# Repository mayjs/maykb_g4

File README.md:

# maykb G4

This is my fourth custom split keyboard, this time using an ANSI layout.

## Caveats / Known Issues

In its current form, the level shifter for the WS2812b LEDs does NOT work.
With most clones, you can just remove the Mosfet and the two resistors next to it and bridge the microcontroller LED data input directly to the LED data input.
Some LEDs might not properly recognize the 3.3V signal though, so you might see some glitches due to this.

Otherwise, the keyboard works without any issues.

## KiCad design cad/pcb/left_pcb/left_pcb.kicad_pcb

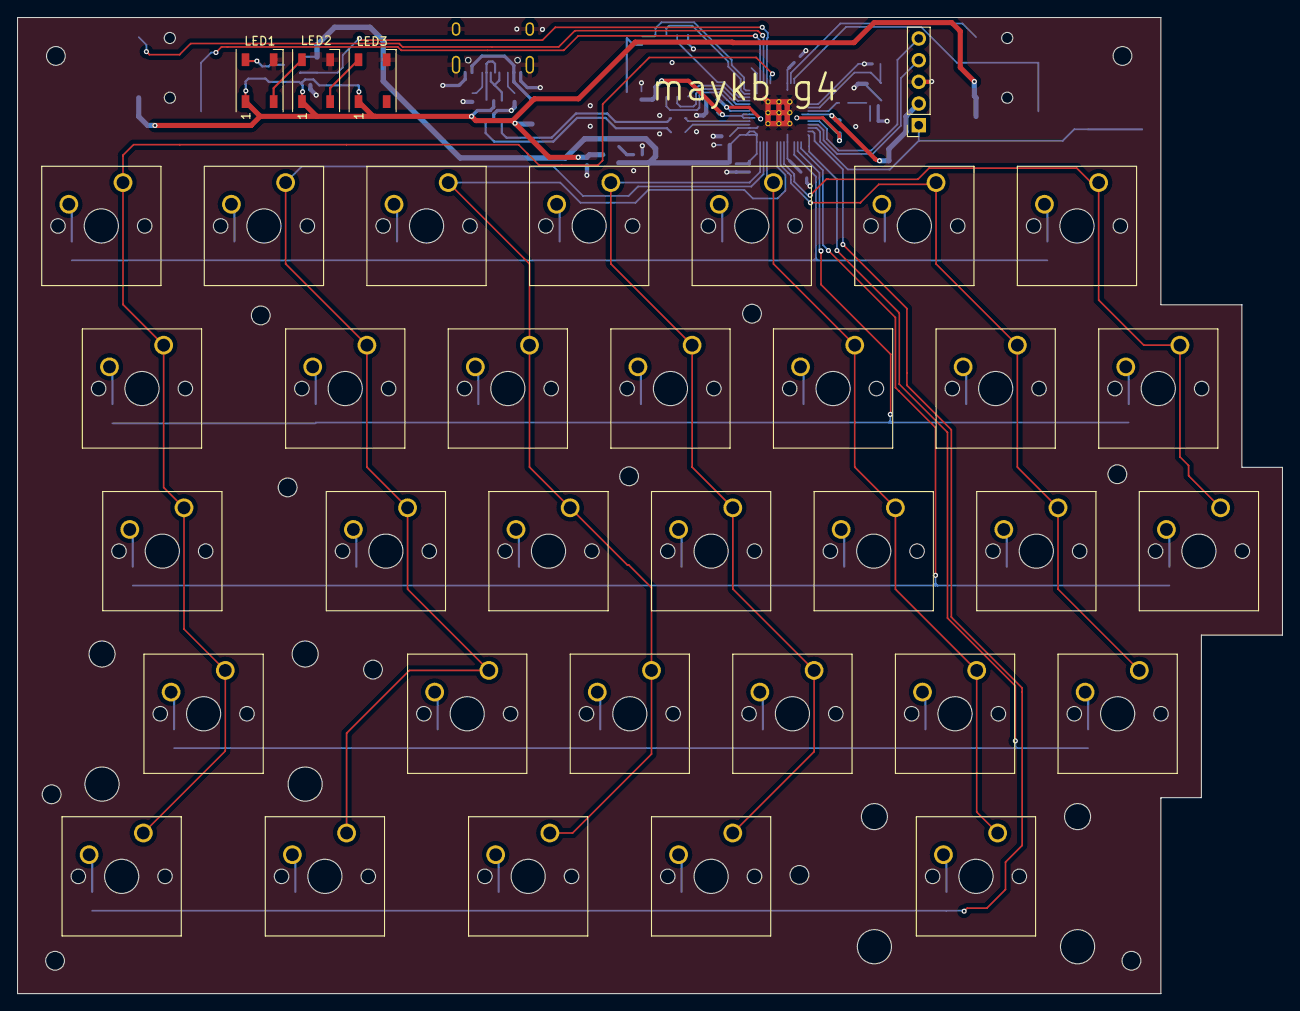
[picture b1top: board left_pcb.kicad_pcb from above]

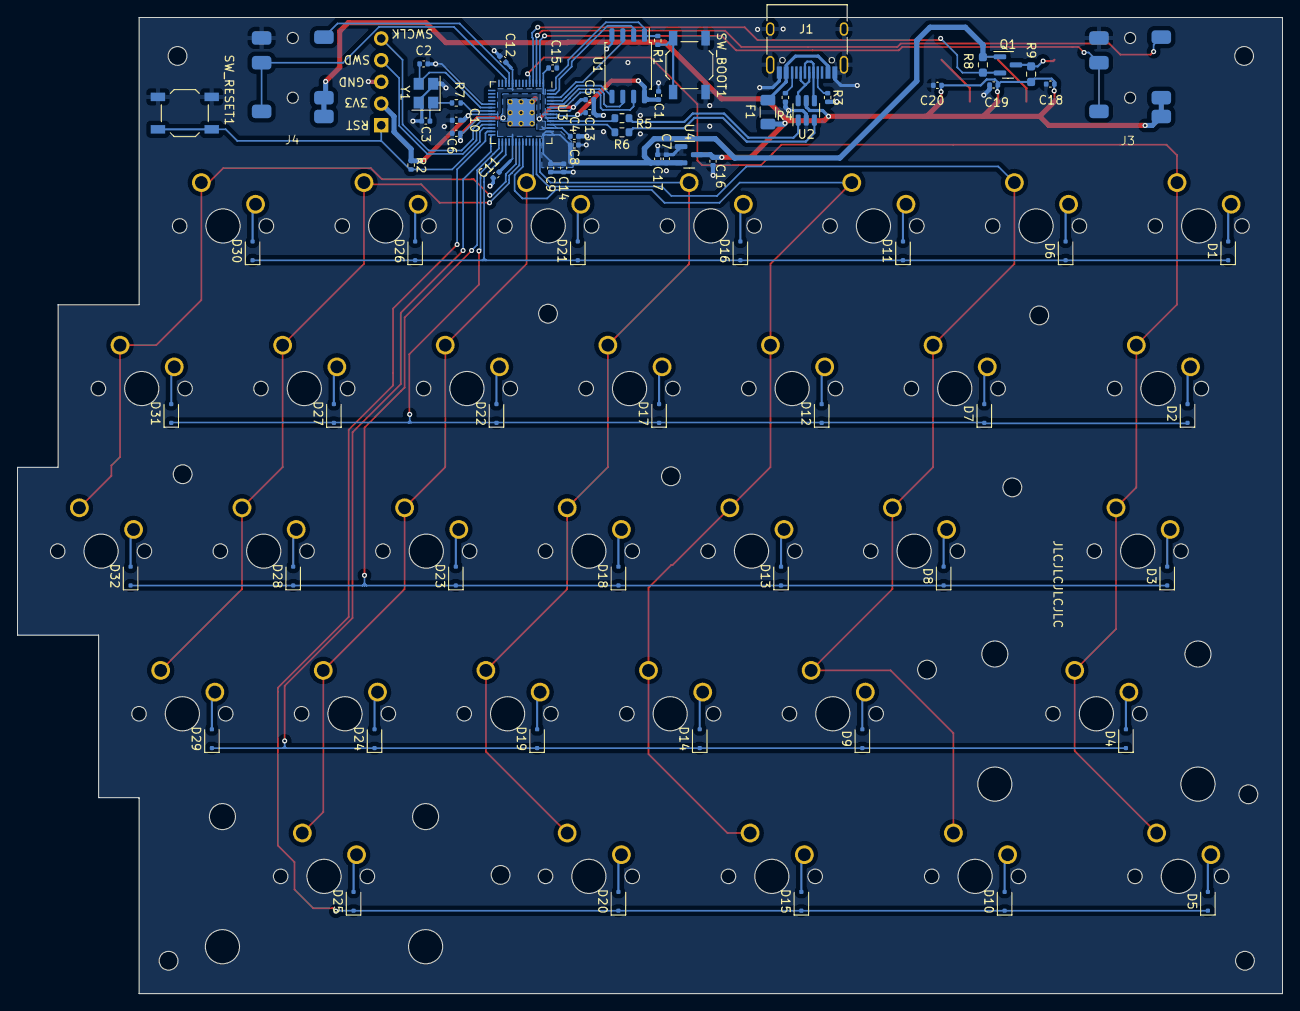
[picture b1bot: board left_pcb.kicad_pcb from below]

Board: 2 copper layers, 148.2 x 114.4 mm, 109 parts (73 on the bottom side), 78 nets.

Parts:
C1, C5, C6, C9, C10, C11, C12, C13, C14, C15, C18, C19, C20: 100nF; C_0402_1005Metric
C2, C3: 22pF; C_0402_1005Metric
C4, C8, C16, C17: 1uF; C_0402_1005Metric
C7: 10uF; C_0402_1005Metric
D1, D2, D3, D4, D5, D6, D7, D8, D9, D10, D11, D12, D13, D14, D15, D16, D17, D18, D19, D20, D21, D22, D23, D24, D25, D26, D27, D28, D29, D30, D31, D32: D; D_SOD-323F
F1: 500mA; Fuse_1206_3216Metric
J1: USB_C_Receptacle_USB2.0; USB_C_Receptacle_HRO_TYPE-C-31-M-12
J2: SWD; PinSocket_1x05_P2.54mm_Vertical
J3: ConnLeft; PJ-342B
J4: ConnRight; PJ-342B
LED1, LED2, LED3: WS2812B; LED_WS2812B_PLCC4_5.0x5.0mm_P3.2mm
Q1: BSS138; SOT-23
R1, R2, R7: 1k; R_0402_1005Metric
R3, R4: 5k1; R_0402_1005Metric
R5, R6: 27R; R_0603_1608Metric
R8, R9: 10k; R_0603_1608Metric_Pad0.98x0.95mm_HandSolder
SW1, SW6, SW7, SW8, SW9, SW11, SW12, SW13, SW14, SW16, SW17, SW18, SW19, SW20, SW21, SW22, SW23, SW24, SW26, SW27, SW28, SW29, SW30, SW31, SW32: SW_Push_45deg; SW_Cherry_MX_1.00u_PCB
SW2: SW_Push_45deg; SW_Cherry_MX_1.50u_PCB
SW3: SW_Push_45deg; SW_Cherry_MX_1.75u_PCB
SW4, SW25: SW_Push_45deg; SW_Cherry_MX_2.25u_PCB
SW5, SW10, SW15: SW_Push_45deg; SW_Cherry_MX_1.25u_PCB
SW_BOOT1: SW_Push; SW_SPST_TL3342
SW_RESET1: SW_Push; SW_SPST_TL3342
U1: W25Q128JVS; SOIC-8_5.23x5.23mm_P1.27mm
U2: USBLC6-2SC6; SOT-23-6
U3: RP2040; RP2040-QFN-56
U4: XC6206PxxxMR-Regulator_Linear; SOT-23
Y1: 12MHz; Crystal_SMD_3225-4Pin_3.2x2.5mm

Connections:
+1V1: C4.1, C5.1, C6.1, U3.23 (DVDD), U3.45 (VREG_VOUT), U3.50 (DVDD)
+3.3V: C1.1, C7.1, C8.1, C9.1, C10.1, C11.1, C12.1, C13.1, C14.1, C15.1, C17.2, J2.2, Q1.1 (G), R2.1, R8.1, U1.8 (VCC), U3.1 (IOVDD), U3.10 (IOVDD), U3.22 (IOVDD), U3.33 (IOVDD), U3.42 (IOVDD), U3.43 (ADC_AVDD), U3.44 (VREG_VIN), U3.48 (USB_VDD), U3.49 (IOVDD), U4.2 (VO)
+5V: C16.2, C18.1, C19.1, C20.1, F1.2, J3.T, J4.T, LED1.1 (VDD), LED2.1 (VDD), LED3.1 (VDD), R9.1, U2.5 (VBUS), U4.3 (VI)
/COL1: SW1.1, SW2.1, SW3.1, SW4.1, SW5.1, U3.5 (GPIO3)
/COL2: SW6.1, SW7.1, SW8.1, SW9.1, SW10.1, U3.40 (GPIO28/ADC2)
/COL3: SW11.1, SW12.1, SW13.1, SW14.1, SW15.1, U3.36 (GPIO24)
/COL4: SW16.1, SW17.1, SW18.1, SW19.1, SW20.1, U3.41 (GPIO29/ADC3)
/COL5: SW21.1, SW22.1, SW23.1, SW24.1, SW25.1, U3.39 (GPIO27/ADC1)
/COL6: SW26.1, SW27.1, SW28.1, SW29.1, U3.35 (GPIO23)
/COL7: SW30.1, SW31.1, SW32.1, U3.34 (GPIO22)
/LED_DATA: Q1.2 (S), R8.2, U3.4 (GPIO2)
/LEFT_RX: J3.R2, U3.3 (GPIO1)
/LEFT_TX: J3.R1, U3.2 (GPIO0)
/RIGHT_RX: J4.R1, U3.12 (GPIO9)
/RIGHT_TX: J4.R2, U3.11 (GPIO8)
/ROW1: D1.1 (K), D6.1 (K), D11.1 (K), D16.1 (K), D21.1 (K), D26.1 (K), D30.1 (K), U3.31 (GPIO20)
/ROW2: D2.1 (K), D7.1 (K), D12.1 (K), D17.1 (K), D22.1 (K), D27.1 (K), D31.1 (K), U3.30 (GPIO19)
/ROW3: D3.1 (K), D8.1 (K), D13.1 (K), D18.1 (K), D23.1 (K), D28.1 (K), D32.1 (K), U3.29 (GPIO18)
/ROW4: D4.1 (K), D9.1 (K), D14.1 (K), D19.1 (K), D24.1 (K), D29.1 (K), U3.28 (GPIO17)
/ROW5: D5.1 (K), D10.1 (K), D15.1 (K), D20.1 (K), D25.1 (K), U3.27 (GPIO16)
/pi-pico/CC1: J1.A5 (CC1), R3.1
/pi-pico/CC2: J1.B5 (CC2), R4.1
/pi-pico/D_+: R5.2, U3.47 (D+)
/pi-pico/D_-: R6.2, U3.46 (D-)
/pi-pico/XTAL_O: C3.2, R7.1, Y1.1
/pi-pico/~USB_BOOT: R1.1, SW_BOOT1.2
CS: R1.2, U1.1 (~CS), U3.56 (QSPI_SS_N)
D_N: R6.1, U2.3 (I/O2)
D_P: R5.1, U2.1 (I/O1)
D_USB_N: J1.A7 (D-), J1.B7 (D-), U2.4 (I/O2)
D_USB_P: J1.A6 (D+), J1.B6 (D+), U2.6 (I/O1)
GND: C1.2, C2.1, C3.1, C4.2, C5.2, C6.2, C7.2, C8.2, C9.2, C10.2, C11.2, C12.2, C13.2, C14.2, C15.2, C16.1, C17.1, C18.2, C19.2, C20.2, J1.A1 (GND), J1.A12 (GND), J1.B1 (GND), J1.B12 (GND), J1.S1 (SHIELD), J2.3, J3.S, J4.S, LED1.3 (VSS), LED2.3 (VSS), LED3.3 (VSS), R3.2, R4.2, SW_BOOT1.1, SW_RESET1.1, U1.4 (GND), U2.2 (GND), U3.19 (TESTEN), U3.57 (GND), U4.1 (GND), Y1.2, Y1.4
unnamed: D1.2 (A), SW1.2
unnamed: D2.2 (A), SW2.2
unnamed: D3.2 (A), SW3.2
unnamed: D4.2 (A), SW4.2
unnamed: D5.2 (A), SW5.2
unnamed: D6.2 (A), SW6.2
unnamed: D7.2 (A), SW7.2
unnamed: D8.2 (A), SW8.2
unnamed: D9.2 (A), SW9.2
unnamed: D10.2 (A), SW10.2
unnamed: D11.2 (A), SW11.2
unnamed: D12.2 (A), SW12.2
unnamed: D13.2 (A), SW13.2
unnamed: D14.2 (A), SW14.2
unnamed: D15.2 (A), SW15.2
unnamed: D16.2 (A), SW16.2
unnamed: D17.2 (A), SW17.2
unnamed: D18.2 (A), SW18.2
unnamed: D19.2 (A), SW19.2
unnamed: D20.2 (A), SW20.2
unnamed: D21.2 (A), SW21.2
unnamed: D22.2 (A), SW22.2
unnamed: D23.2 (A), SW23.2
unnamed: D24.2 (A), SW24.2
unnamed: D25.2 (A), SW25.2
unnamed: D26.2 (A), SW26.2
unnamed: D27.2 (A), SW27.2
unnamed: D28.2 (A), SW28.2
unnamed: D29.2 (A), SW29.2
unnamed: D30.2 (A), SW30.2
unnamed: D31.2 (A), SW31.2
unnamed: D32.2 (A), SW32.2
unnamed: LED1.4 (DIN), Q1.3 (D), R9.2
unnamed: LED1.2 (DOUT), LED2.4 (DIN)
unnamed: LED2.2 (DOUT), LED3.4 (DIN)
QSPI_CLK: U1.6 (CLK), U3.52 (QSPI_SCLK)
SD0: U1.5 (DI(IO0)), U3.53 (QSPI_SD0)
SD1: U1.2 (DO(IO1)), U3.55 (QSPI_SD1)
SD2: U1.3 (IO2), U3.54 (QSPI_SD2)
SD3: U1.7 (IO3), U3.51 (QSPI_SD3)
SWCLK: J2.5, U3.24 (SWCLK)
SWD: J2.4, U3.25 (SWDIO)
VBUS: F1.1, J1.A4 (VBUS), J1.A9 (VBUS), J1.B4 (VBUS), J1.B9 (VBUS)
XTAL_IN: C2.2, U3.20 (XTAL_IN), Y1.3
XTAL_OUT: R7.2, U3.21 (XTAL_OUT)
~RESET: J2.1, R2.2, SW_RESET1.2, U3.26 (~RUN)

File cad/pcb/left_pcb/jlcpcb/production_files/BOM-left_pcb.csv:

Comment,Designator,Footprint,LCSC
1k,"R1,R2,R7",R_0402_1005Metric,C11702
W25Q128JVS,U1,SOIC-8_5.23x5.23mm_P1.27mm,C131025
100nF,"C1,C10,C11,C12,C13,C14,C15,C18,C19,C20,C5,C6,C9",C_0402_1005Metric,C1525
10uF,C7,C_0402_1005Metric,C15525
22pF,"C2,C3",C_0402_1005Metric,C1555
USB_C_Receptacle_USB2.0,J1,USB_C_Receptacle_HRO_TYPE-C-31-M-12,C165948
RP2040,U3,RP2040-QFN-56,C2040
D,"D1,D10,D11,D12,D13,D14,D15,D16,D17,D18,D19,D2,D20,D21,D22,D23,D24,D25,D26,D27,D28,D29,D3,D30,D31,D32,D4,D5,D6,D7,D8,D9",D_SOD-323F,C2128
27R,"R5,R6",R_0603_1608Metric,C25190
5k1,"R3,R4",R_0402_1005Metric,C25905
USBLC6-2SC6,U2,SOT-23-6,C2827654
1uF,"C16,C17,C4,C8",C_0402_1005Metric,C52923
XC6206PxxxMR-Regulator_Linear,U4,SOT-23,C5446
ConnLeft,"J3,J4",PJ-342B,C668606
500mA,F1,Fuse_1206_3216Metric,C70076
12MHz,Y1,Crystal_SMD_3225-4Pin_3.2x2.5mm,C9002
10k,R8,R_0603_1608Metric_Pad0.98x0.95mm_HandSolder,
BSS138,Q1,SOT-23,
10k,R9,R_0603_1608Metric_Pad0.98x0.95mm_HandSolder,

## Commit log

2024-02-04 Add all of the keyboard components :)
2024-02-25 Update to latest firmware
